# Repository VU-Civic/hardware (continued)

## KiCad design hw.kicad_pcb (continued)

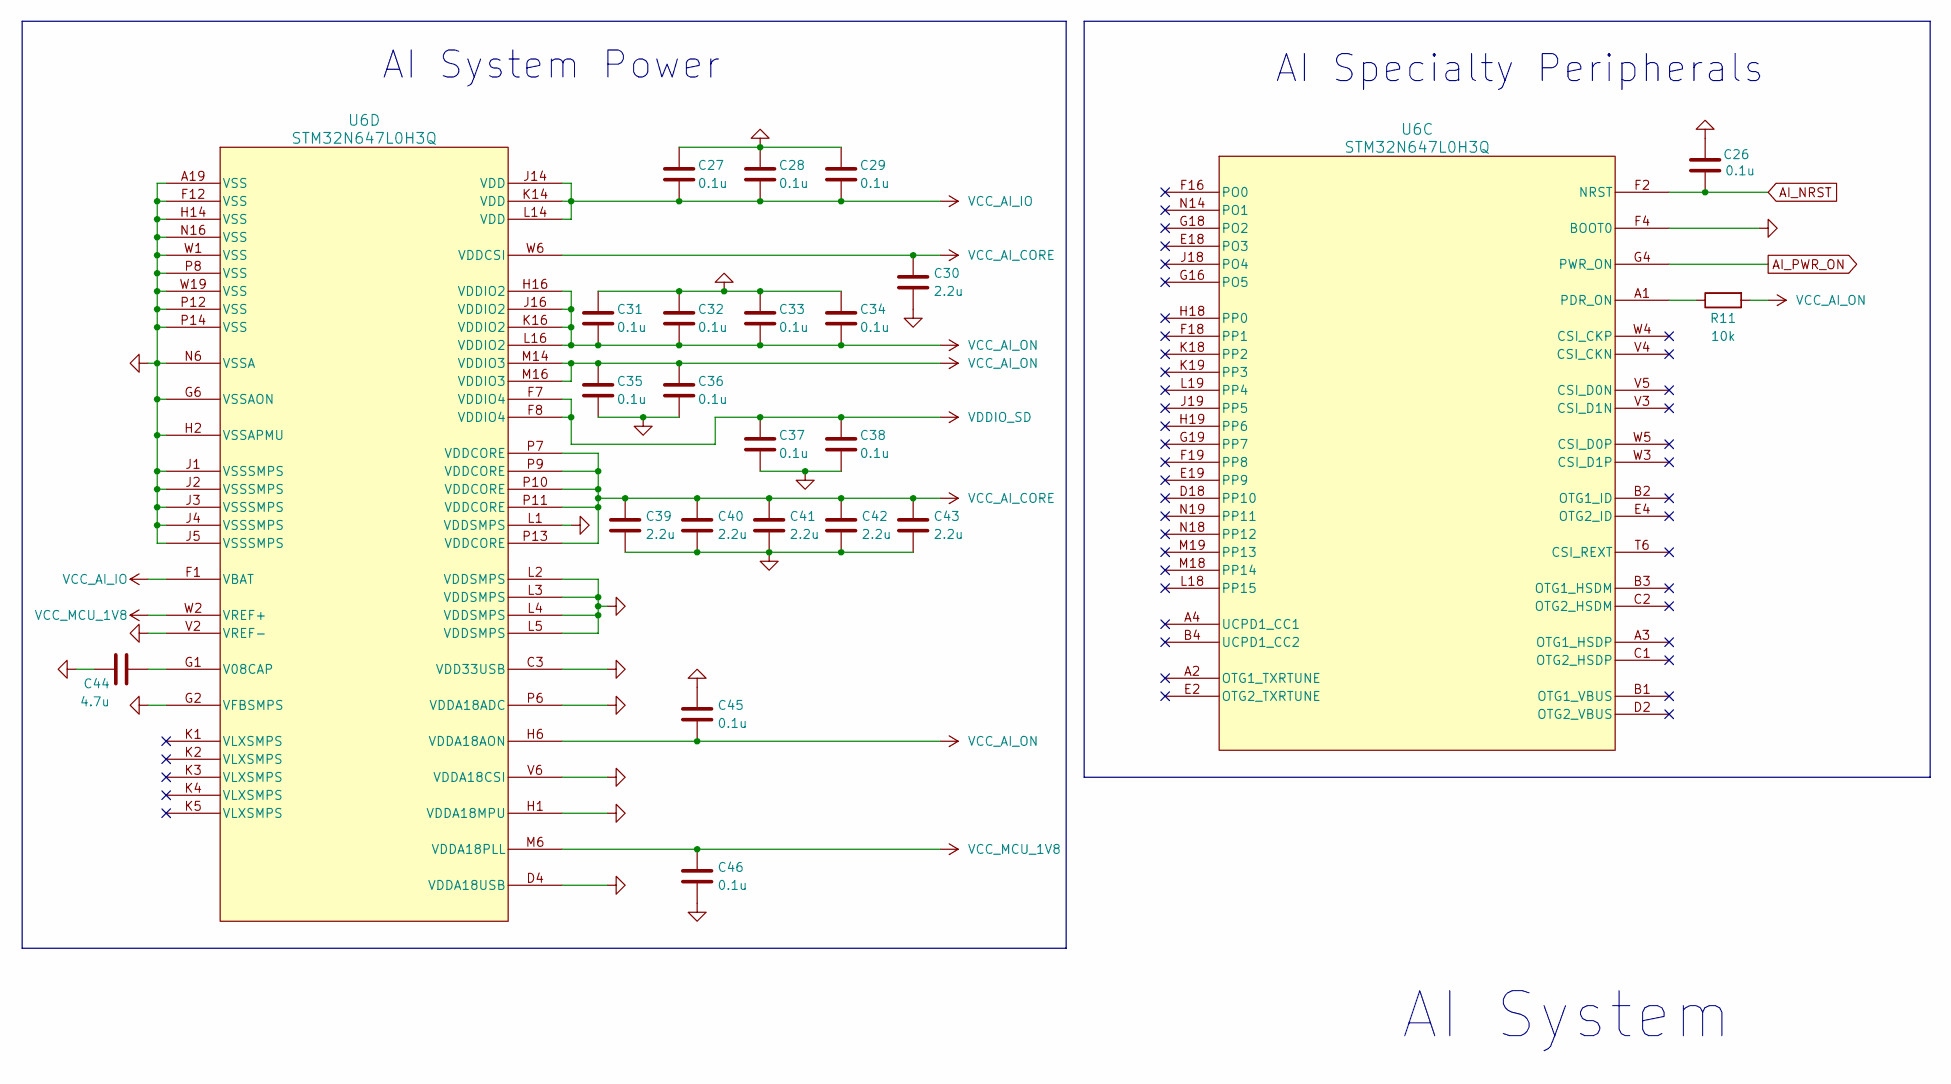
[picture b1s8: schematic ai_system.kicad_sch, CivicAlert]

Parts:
C26, C27, C28, C29, C31, C32, C33, C34, C35, C36, C37, C38, C45, C46: 0.1u; C_0201_0603Metric; MPN GRM033Z71C104KE14D
C30, C39, C40, C41, C42, C43: 2.2u; C_0201_0603Metric; MPN GRT033D70J105ME13D
C44: 4.7u; C_0402_1005Metric; MPN GRT155D70J475ME13D
R11: 10k; R_0402_1005Metric
U6: STM32N647L0H3Q; MPN STM32N647L0H3Q

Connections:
AI_NRST: C26.1, U6.F2 (NRST); also elsewhere on the board
AI_PWR_ON: U6.G4 (PWR_ON); also elsewhere on the board
GND: C26.2, C27.1, C28.1, C29.1, C30.2, C31.1, C32.1, C33.1, C34.1, C35.2, C36.2, C37.2, C38.2, C39.2, C40.2, C41.2, C42.2, C43.2, C44.2, C45.1, C46.2, U6.A19 (VSS), U6.C3 (VDD33USB), U6.D4 (VDDA18USB), U6.F4 (BOOT0), U6.F12 (VSS), U6.G2 (VFBSMPS), U6.G6 (VSSAON), U6.H1 (VDDA18MPU), U6.H2 (VSSAPMU), U6.H14 (VSS), U6.J1 (VSSSMPS), U6.J2 (VSSSMPS), U6.J3 (VSSSMPS), U6.J4 (VSSSMPS), U6.J5 (VSSSMPS), U6.L1 (VDDSMPS), U6.L2 (VDDSMPS), U6.L3 (VDDSMPS), U6.L4 (VDDSMPS), U6.L5 (VDDSMPS), U6.N6 (VSSA), U6.N16 (VSS), U6.P6 (VDDA18ADC), U6.P8 (VSS), U6.P12 (VSS), U6.P14 (VSS), U6.V2 (VREF-), U6.V6 (VDDA18CSI), U6.W1 (VSS), U6.W19 (VSS); also elsewhere on the board
unnamed: R11.1, U6.A1 (PDR_ON)
unnamed: C44.1, U6.G1 (V08CAP)
VCC_AI_CORE: C30.1, C39.1, C40.1, C41.1, C42.1, C43.1, U6.P7 (VDDCORE), U6.P9 (VDDCORE), U6.P10 (VDDCORE), U6.P11 (VDDCORE), U6.P13 (VDDCORE), U6.W6 (VDDCSI); also elsewhere on the board
VCC_AI_IO: C27.2, C28.2, C29.2, U6.F1 (VBAT), U6.J14 (VDD), U6.K14 (VDD), U6.L14 (VDD); also elsewhere on the board
VCC_AI_ON: C31.2, C32.2, C33.2, C34.2, C35.1, C36.1, C45.2, R11.2, U6.H6 (VDDA18AON), U6.H16 (VDDIO2), U6.J16 (VDDIO2), U6.K16 (VDDIO2), U6.L16 (VDDIO2), U6.M14 (VDDIO3), U6.M16 (VDDIO3); also elsewhere on the board
VCC_MCU_1V8: C46.1, U6.M6 (VDDA18PLL), U6.W2 (VREF+); also elsewhere on the board
VDDIO_SD: C37.1, C38.1, U6.F7 (VDDIO4), U6.F8 (VDDIO4); also elsewhere on the board

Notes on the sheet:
AI System Power
AI Specialty Peripherals
AI System

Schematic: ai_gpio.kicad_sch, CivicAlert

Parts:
R12: 22; R_0402_1005Metric
R13, R14: 10k; R_0402_1005Metric
R63, R64: 2.2k; R_0402_1005Metric
U6: STM32N647L0H3Q; MPN STM32N647L0H3Q

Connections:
AI_BOOT_DEV: U6.T10 (PA6); also elsewhere on the board
AI_DATA_IN_CS: U6.T15 (PA15); also elsewhere on the board
AI_DATA_IN_MISO: U6.W15 (PB4); also elsewhere on the board
AI_DATA_IN_MOSI: U6.V15 (PA7); also elsewhere on the board
AI_DATA_IN_SCK: U6.V10 (PA5); also elsewhere on the board
AI_DATA_OUT_SCL: R64.1, U6.T9 (PA8); also elsewhere on the board
AI_DATA_OUT_SDA: R63.1, U6.V9 (PA9); also elsewhere on the board
AI_HOST_WAKEUP: U6.W12 (PA1); also elsewhere on the board
AI_OVERDRIVE: U6.V1 (PF13); also elsewhere on the board
AI_SWCLK: U6.V7 (PA14); also elsewhere on the board
AI_SWDIO: R12.1; also elsewhere on the board
FLASH_CLK: U6.U19 (PN6); also elsewhere on the board
FLASH_DQS: U6.R19 (PN0); also elsewhere on the board
FLASH_IO0: U6.T19 (PN2); also elsewhere on the board
FLASH_IO1: U6.P19 (PN3); also elsewhere on the board
FLASH_IO2: U6.V19 (PN4); also elsewhere on the board
FLASH_IO3: U6.U18 (PN5); also elsewhere on the board
FLASH_IO4: U6.V18 (PN8); also elsewhere on the board
FLASH_IO5: U6.T18 (PN9); also elsewhere on the board
FLASH_IO6: U6.R18 (PN10); also elsewhere on the board
FLASH_IO7: U6.P18 (PN11); also elsewhere on the board
FLASH_NCS: U6.P16 (PN1); also elsewhere on the board
GND: R13.1, R14.1; also elsewhere on the board
unnamed: R12.2, U6.W7 (PA13)
unnamed: R14.2, U6.E1 (PC14-OSC32_IN)
unnamed: R13.2, U6.A5 (PH0-OSC_IN)
SD_CARD_DETECT: U6.W18 (PN12); also elsewhere on the board
SD_CARD_EN: U6.B19 (PE2); also elsewhere on the board
SD_CLK: U6.A6 (PC12); also elsewhere on the board
SD_CMD: U6.D7 (PH2); also elsewhere on the board
SD_DAT0: U6.F6 (PC8); also elsewhere on the board
SD_DAT1: U6.D5 (PC9); also elsewhere on the board
SD_DAT2: U6.D6 (PC10); also elsewhere on the board
SD_DAT3: U6.B6 (PC11); also elsewhere on the board
SD_PWR_SELECT: U6.A18 (PE0); also elsewhere on the board
VCC_MCU_1V8: R63.2, R64.2; also elsewhere on the board

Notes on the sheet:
AI Clocks and GPIO
AI GPIO Banks A-D
AI GPIO Banks E-N

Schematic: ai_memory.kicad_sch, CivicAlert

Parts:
B1: 009159010061911
BOOT1: PTS810; MPN PTS810
C51, C54, C55: 0.1u; C_0402_1005Metric; MPN GRM155R71C104KA88J
C52, C53, C56: 4.7u; C_0402_1005Metric; MPN GRT155D70J475ME13D
CR6: BAT854W,115; BAT854AW,115; MPN BAT854W,115
IC1: MX25UM25645GXDI00-T; MX25UM25645GXDI00; MPN MX25UM25645GXDI00-T
IC2: ESDALC6V1W5; MPN ESDALC6V1W5
R15, R16, R17, R62: 10k; R_0402_1005Metric
R18, R19: 22; R_0402_1005Metric

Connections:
AI_BOOT_DEV: BOOT1.1, BOOT1.2, R62.2; also elsewhere on the board
AI_NRST: B1.9 (NRST), CR6.3, IC2.5 (I/04); also elsewhere on the board
AI_SWCLK: IC2.4 (I/03), R19.1; also elsewhere on the board
AI_SWDIO: IC2.3 (I/02), R18.1; also elsewhere on the board
AI_SWO: B1.5 (JTDO/SWO), IC2.1 (I/01)
FLASH_CLK: IC1.B2 (SCLK); also elsewhere on the board
FLASH_DQS: IC1.C3 (DQS); also elsewhere on the board
FLASH_IO0: IC1.D3 (SIO0); also elsewhere on the board
FLASH_IO1: IC1.D2 (SIO1); also elsewhere on the board
FLASH_IO2: IC1.C4 (SIO2); also elsewhere on the board
FLASH_IO3: IC1.D4 (SIO3); also elsewhere on the board
FLASH_IO4: IC1.D5 (SIO4); also elsewhere on the board
FLASH_IO5: IC1.E3 (SIO5); also elsewhere on the board
FLASH_IO6: IC1.E2 (SIO6); also elsewhere on the board
FLASH_IO7: IC1.E1 (SIO7); also elsewhere on the board
FLASH_NCS: IC1.C2 (CS#), R17.2; also elsewhere on the board
GND: B1.6 (GND), C51.2, C52.2, C53.2, C54.2, C55.2, C56.2, IC1.B3 (GND), IC1.C1 (VSSQ_1), IC1.E5 (VSSQ_2), IC2.2 (GND), R62.1; also elsewhere on the board
unnamed: B1.4 (JCLK/SWCLK), R19.2
unnamed: B1.3 (JTMS/SWDIO), R18.2
unnamed: IC1.A5 (ECS#), R16.2
unnamed: CR6.1, IC1.A4 (RESET#), R15.1
VCC_AI_IO: B1.10 (VCC), BOOT1.3, BOOT1.4; also elsewhere on the board
VCC_AI_ON: C51.1, C52.1, C53.1, C54.1, C55.1, C56.1, IC1.B4 (VCC), IC1.D1 (VCCQ_1), IC1.E4 (VCCQ_2), R15.2, R16.1, R17.1; also elsewhere on the board

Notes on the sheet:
AI Memory + Debug
Flash Memory
AI JTAG/SWD Connector
Boot Mode Switch

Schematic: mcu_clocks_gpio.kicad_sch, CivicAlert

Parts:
C82: 10n; C_0402_1005Metric; MPN GCM155R71H103KA55D
C83, C85: 0.1u; C_0402_1005Metric; MPN GRM155R71C104KA88J
C84, C86: 3.3p; C_0402_1005Metric; MPN GRT1555C1H3R3CA02J
R32, R34, R38: 22; R_0402_1005Metric
R33, R35: 47; R_0402_1005Metric
R36, R37: 10k; R_0402_1005Metric
U11: STM32H745ZIT6; MPN STM32H745ZIT6
Y3: ATX-H11-F-25.000MHz-F25-T; ATX-H11-F-25_000MHz-F25-T; MPN ATX-H11-F-25.000MHz-F25-T
Y4: ABS07AIG-32.768KHZ-7-T; ABS07AIG_32_768KHZ_7_T; MPN ABS07AIG-32.768KHZ-7-T

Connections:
AI_DATA_IN_CS: U11.72 (PB12); also elsewhere on the board
AI_DATA_IN_MISO: U11.74 (PB14); also elsewhere on the board
AI_DATA_IN_MOSI: U11.75 (PB15); also elsewhere on the board
AI_DATA_IN_SCK: U11.73 (PB13); also elsewhere on the board
AI_DATA_OUT_SCL: U11.97 (PA8); also elsewhere on the board
AI_DATA_OUT_SDA: U11.96 (PC9); also elsewhere on the board
AI_HOST_WAKEUP: U11.94 (PC7); also elsewhere on the board
AUDIO_CLK: R33.1; also elsewhere on the board
AUDIO_FSYNC: R35.1; also elsewhere on the board
AUDIO_SD: U11.61 (PE11); also elsewhere on the board
CELL_UART_CTS: U11.37 (PA0); also elsewhere on the board
CELL_UART_RTS: U11.38 (PA1); also elsewhere on the board
CELL_UART_RXD: U11.40 (PA3); also elsewhere on the board
CELL_UART_TXD: U11.39 (PA2); also elsewhere on the board
GND: C82.2, C83.2, C84.2, C85.2, C86.2, R36.2, Y3.2 (GND); also elsewhere on the board
GPS_NRESET: U11.44 (PA5); also elsewhere on the board
GPS_PWR_ON: U11.43 (PA4); also elsewhere on the board
GPS_TIMEPULSE: U11.60 (PE10); also elsewhere on the board
GPS_TIME_TRIGGER: U11.59 (PE9); also elsewhere on the board
GPS_UART_RXD: U11.57 (PE7); also elsewhere on the board
GPS_UART_TXD: U11.58 (PE8); also elsewhere on the board
IMU_INT: U11.133 (PB6); also elsewhere on the board
IMU_SCL: U11.136 (PB8); also elsewhere on the board
IMU_SDA: U11.134 (PB7); also elsewhere on the board
LED_GPS_STATUS: U11.50 (PB1); also elsewhere on the board
MCU_NRST: C85.1, U11.27 (NRST); also elsewhere on the board
MCU_SWDCLK: U11.107 (PA14); also elsewhere on the board
MCU_SWDIO: R34.1; also elsewhere on the board
MCU_SWO: R38.1; also elsewhere on the board
MICS_SCL: U11.66 (PB10); also elsewhere on the board
MICS_SDA: U11.67 (PB11); also elsewhere on the board
unnamed: R34.2, U11.102 (PA13)
unnamed: R38.2, U11.130 (PB3)
unnamed: C84.1, U11.10 (PC14-OSC32_IN), Y4.1
unnamed: C86.1, U11.11 (PC15-OSC32_OUT), Y4.2
unnamed: R36.1, U11.135 (BOOT0)
unnamed: R37.1, U11.142 (PDR_ON)
unnamed: R33.2, U11.62 (PE12)
unnamed: R35.2, U11.63 (PE13)
unnamed: R32.1, U11.25 (PH0-OSC_IN)
unnamed: R32.2, Y3.3 (OUTPUT)
USB_D+: U11.101 (PA12); also elsewhere on the board
USB_D-: U11.100 (PA11); also elsewhere on the board
VCC_MCU: R37.2; also elsewhere on the board
VCC_MCU_1V8: C82.1, C83.1, Y3.1 (~INH), Y3.4 (VDD); also elsewhere on the board

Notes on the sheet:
MCU Clocks and GPIO
MCU GPIO Banks E-G
MCU GPIO Banks A-D

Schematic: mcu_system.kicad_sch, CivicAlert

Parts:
C62, C76, C79: 4.7u; C_0402_1005Metric; MPN GRT155D70J475ME13D
C63, C64, C65, C66, C67, C68, C69, C70, C71, C72, C73, C74, C75, C77: 0.1u; C_0402_1005Metric; MPN GRM155R71C104KA88J
C78, C80, C81: 2.2u; C_0402_1005Metric; MPN GRT155C71A225KE13D
FL1: FCM 1608KF-601T03; FCM1608KF-601T03; MPN FCM1608KF-601T03
R28: 47; R_0402_1005Metric
U11: STM32H745ZIT6; MPN STM32H745ZIT6

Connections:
GND: C62.1, C63.1, C64.1, C65.1, C66.1, C67.1, C68.1, C69.2, C70.2, C71.2, C72.2, C73.2, C74.2, C75.2, C76.2, C77.1, C78.2, C79.2, C80.2, C81.2, U11.6 (VSS), U11.12 (VSS), U11.14 (VSSSMPS), U11.16 (VDDSMPS), U11.17 (VFBSMPS), U11.18 (VSS), U11.33 (VSS), U11.34 (VSSA), U11.41 (VSS), U11.55 (VSS), U11.69 (VSS), U11.80 (VSS), U11.89 (VSS), U11.104 (VSS), U11.118 (VSS), U11.128 (VSS), U11.141 (VSS); also elsewhere on the board
unnamed: C80.1, C81.1, U11.68 (VCAP), U11.103 (VCAP), U11.140 (VCAP)
unnamed: C78.1, U11.91 (VDD33USB)
unnamed: FL1.2, R28.1, U11.36 (VDDA)
unnamed: R28.2, U11.35 (VREF+)
VCC_5V: C79.1, U11.90 (VDD50USB); also elsewhere on the board
VCC_MCU: C62.2, C63.2, C64.2, C65.2, C66.2, C67.2, C68.2, C69.1, C70.1, C71.1, C72.1, C73.1, C74.1, C75.1, C76.1, C77.2, FL1.1, U11.7 (VDD), U11.8 (VBAT), U11.13 (VDD), U11.19 (VDD), U11.32 (VDD), U11.42 (VDD), U11.56 (VDD), U11.70 (VDDLDO), U11.71 (VDD), U11.79 (VDD), U11.92 (VDD), U11.105 (VDDLDO), U11.106 (VDD), U11.119 (VDD), U11.129 (VDD), U11.143 (VDDLDO), U11.144 (VDD); also elsewhere on the board

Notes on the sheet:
MCU System
MCU Power

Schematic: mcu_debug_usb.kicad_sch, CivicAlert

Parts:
B2: 009159010061911
C87, C88: 0.1u; C_0402_1005Metric; MPN GRM155R71C104KA88J
IC3: ESDALC6V1W5; MPN ESDALC6V1W5
J1: USB4730-GF-A_REVA; USB4730-GF-A; PARTREV A
R39, R40: 22; R_0402_1005Metric
R41, R42: 5.1k; R_0402_1005Metric

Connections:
GND: B2.6 (GND), C87.2, C88.2, IC3.2 (GND), J1.A1/B12 (GND_A), J1.B1/A12 (GND_B), J1.SH1 (SHELL_GND), J1.SH2 (SHELL_GND), J1.SH3 (SHELL_GND), J1.SH4 (SHELL_GND), R41.1, R42.1; also elsewhere on the board
MCU_NRST: B2.9 (NRST), IC3.5 (I/04); also elsewhere on the board
MCU_SWDCLK: IC3.4 (I/03), R40.1; also elsewhere on the board
MCU_SWDIO: IC3.3 (I/02), R39.1; also elsewhere on the board
MCU_SWO: B2.5 (JTDO/SWO), IC3.1 (I/01); also elsewhere on the board
unnamed: B2.4 (JCLK/SWCLK), R40.2
unnamed: B2.3 (JTMS/SWDIO), R39.2
unnamed: J1.A5 (CC1), R41.2
unnamed: J1.B5 (CC2), R42.2
USB_D+: J1.A6 (DP1), J1.B6 (DP2); also elsewhere on the board
USB_D-: J1.A7 (DN1), J1.B7 (DN2); also elsewhere on the board
VCC_5V: C87.1, C88.1, J1.A4/B9 (VBUS_A), J1.B4/A9 (VBUS_B); also elsewhere on the board
VCC_MCU_1V8: B2.10 (VCC); also elsewhere on the board

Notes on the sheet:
USB-C Power + Aux Data Output
MCU Debug + USB
MCU JTAG/SWD Connector

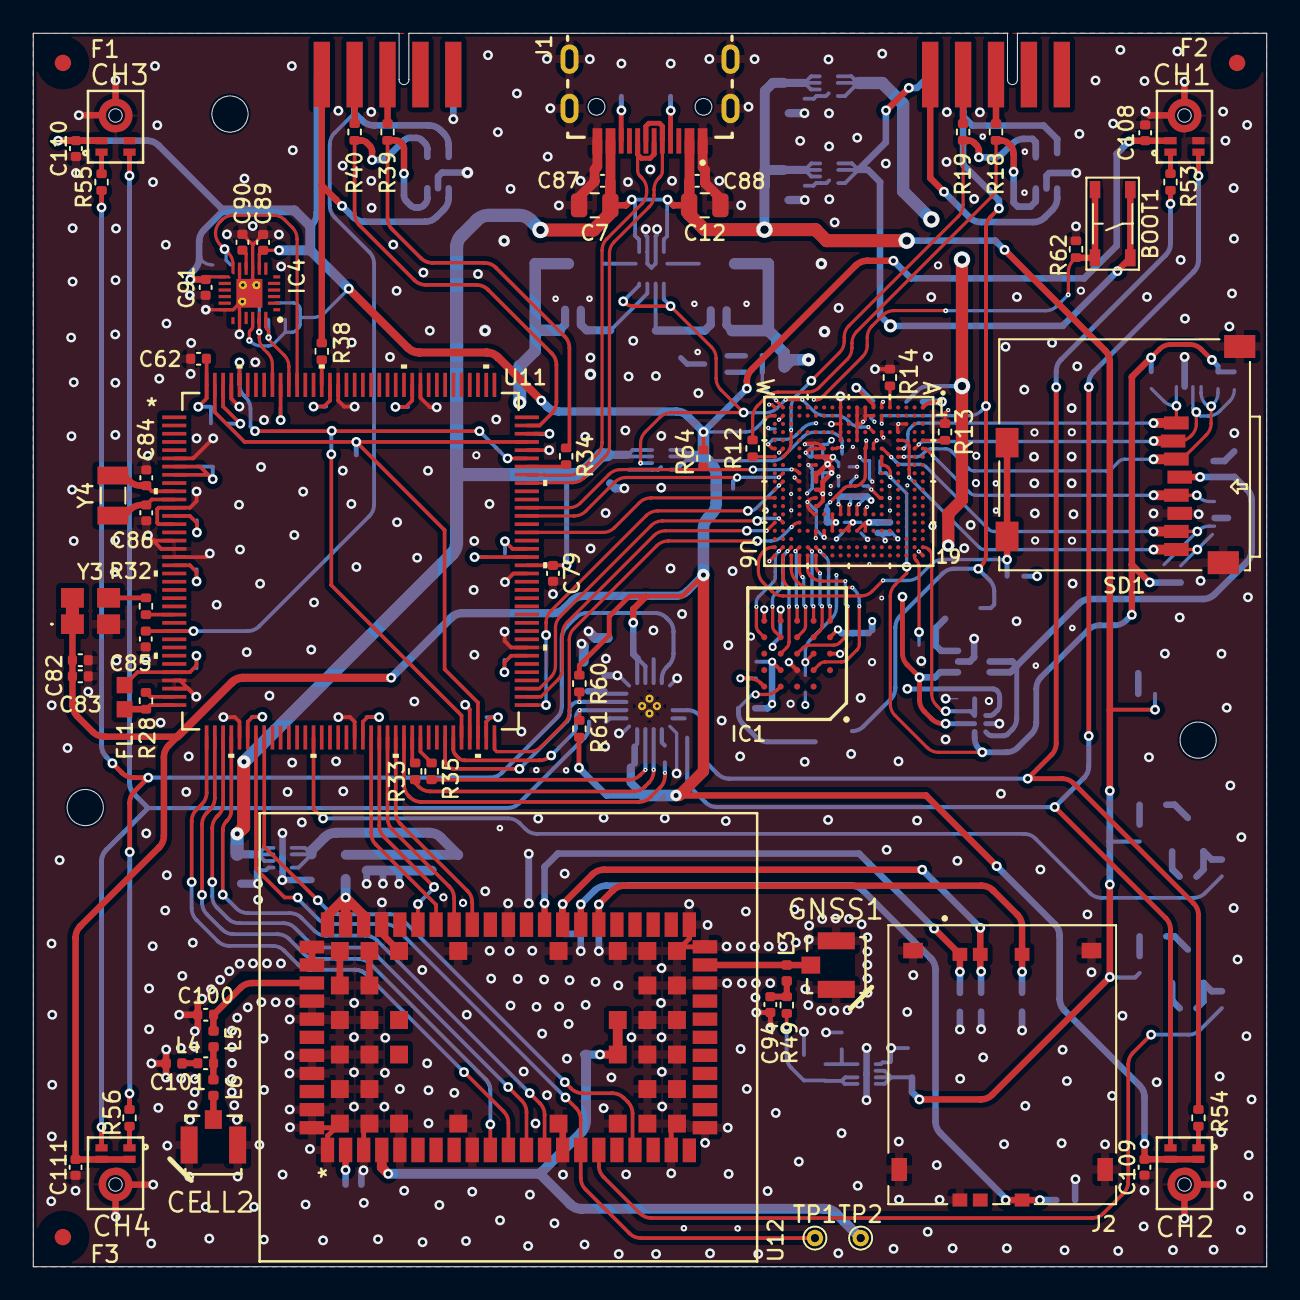
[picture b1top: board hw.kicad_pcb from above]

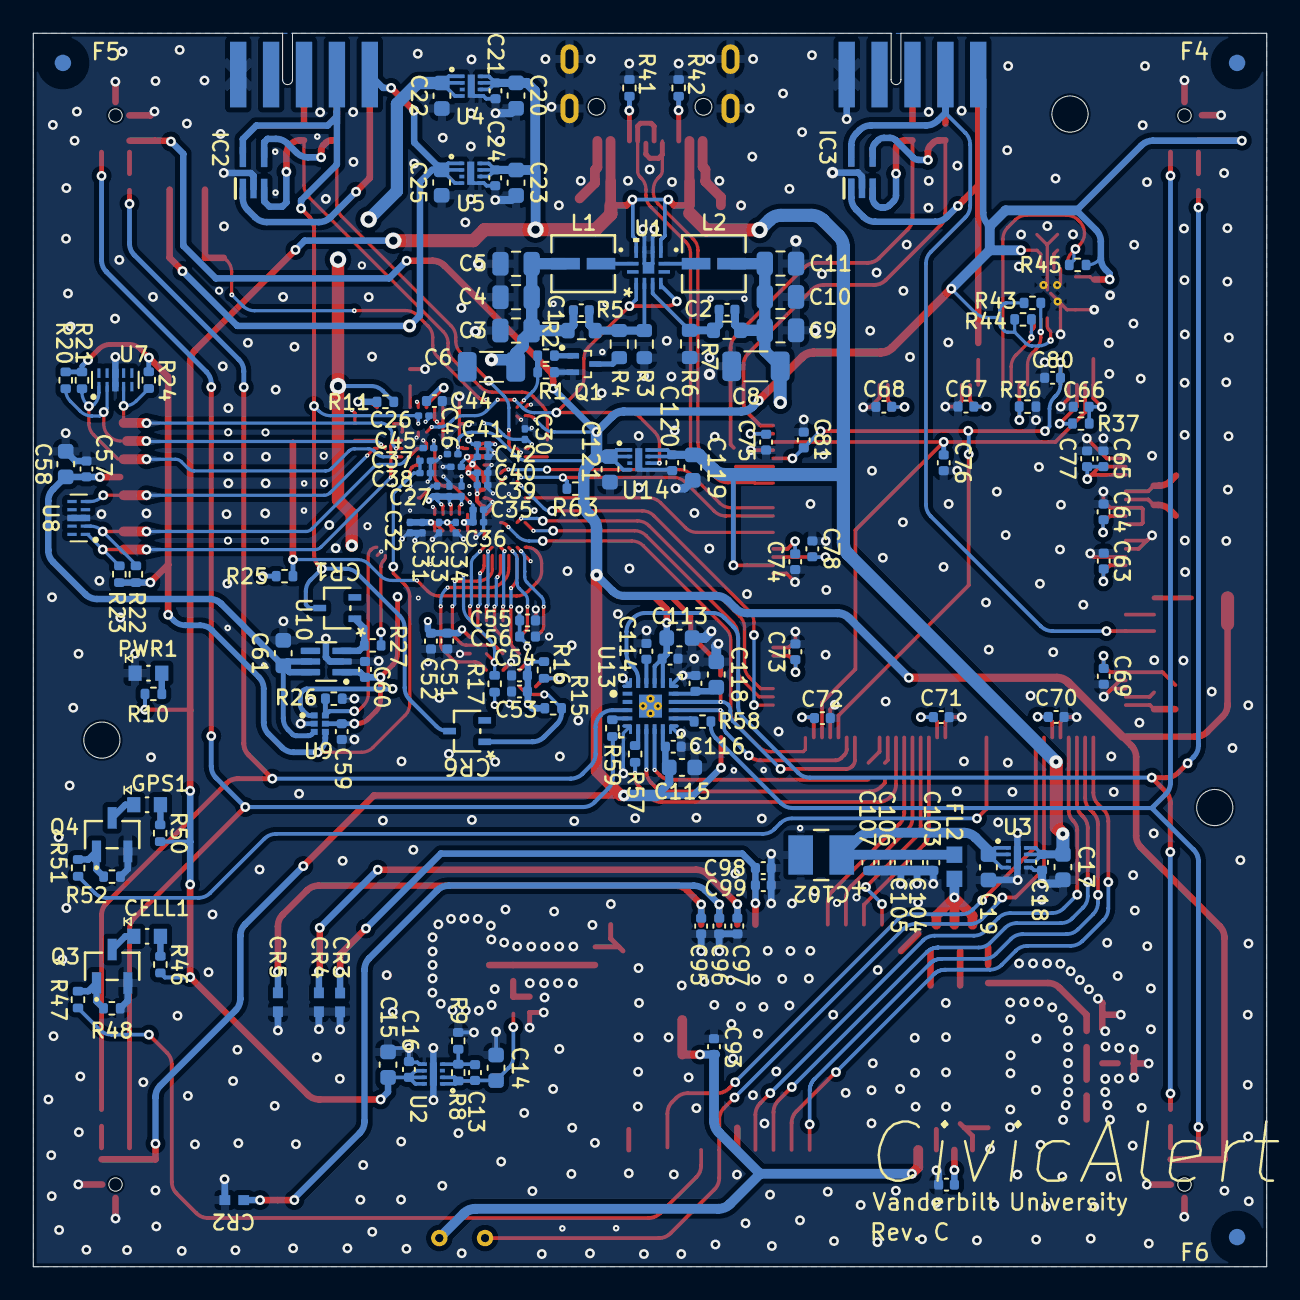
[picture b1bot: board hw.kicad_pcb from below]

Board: 4 copper layers, 75.0 x 75.0 mm, 241 parts (166 on the bottom side), 140 nets.

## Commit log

2025-06-16 Initial Commit (Rev. A)
2025-06-17 Add cathode marker to footprint
2025-06-17 Fix RF trace impedances
2025-06-23 Update silkscreen, add modem +5V via to regulator
2025-07-31 New structure for holding parts, symbols, and footprints
2025-08-01 Update documentation and images
2025-08-01 Add debugger requirements info
2025-09-10 Update for RevB
2025-09-15 Finalize RevB
2025-09-16 Fix wrong silkscreen layout for flash chp
2025-09-16 Add fiducials
2025-11-15 Updates for Rev. C
2025-11-20 Update RevC design
2026-03-02 Connect VREF+ to GND instead of VCC_1.8
